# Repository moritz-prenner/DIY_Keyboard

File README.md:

# DIY_Keyboard 

This project is a full size Keyboard powered by a rp2040 pro micro and a custom pcb designed by myself :)
After I am going to build it it should (hopefully) function like a regular storebought keyboard. It even contains a knob to control volume for example.
I built this project to get better at pcb design and learn something new about keyboard firmware.

Note for the reviewer:

As you probably already seen, my total (in the bom) is around 95$. But this number is without the filament cost for the printing of the case. 
Even tho I am probably going to spend my tickets I am going to earn with this project on filament, I still estimated the cost and added it to the bom total.
That makes my funding request (around 120 - 130 $) - of course I am going to return the rest if it is cheaper than expected.

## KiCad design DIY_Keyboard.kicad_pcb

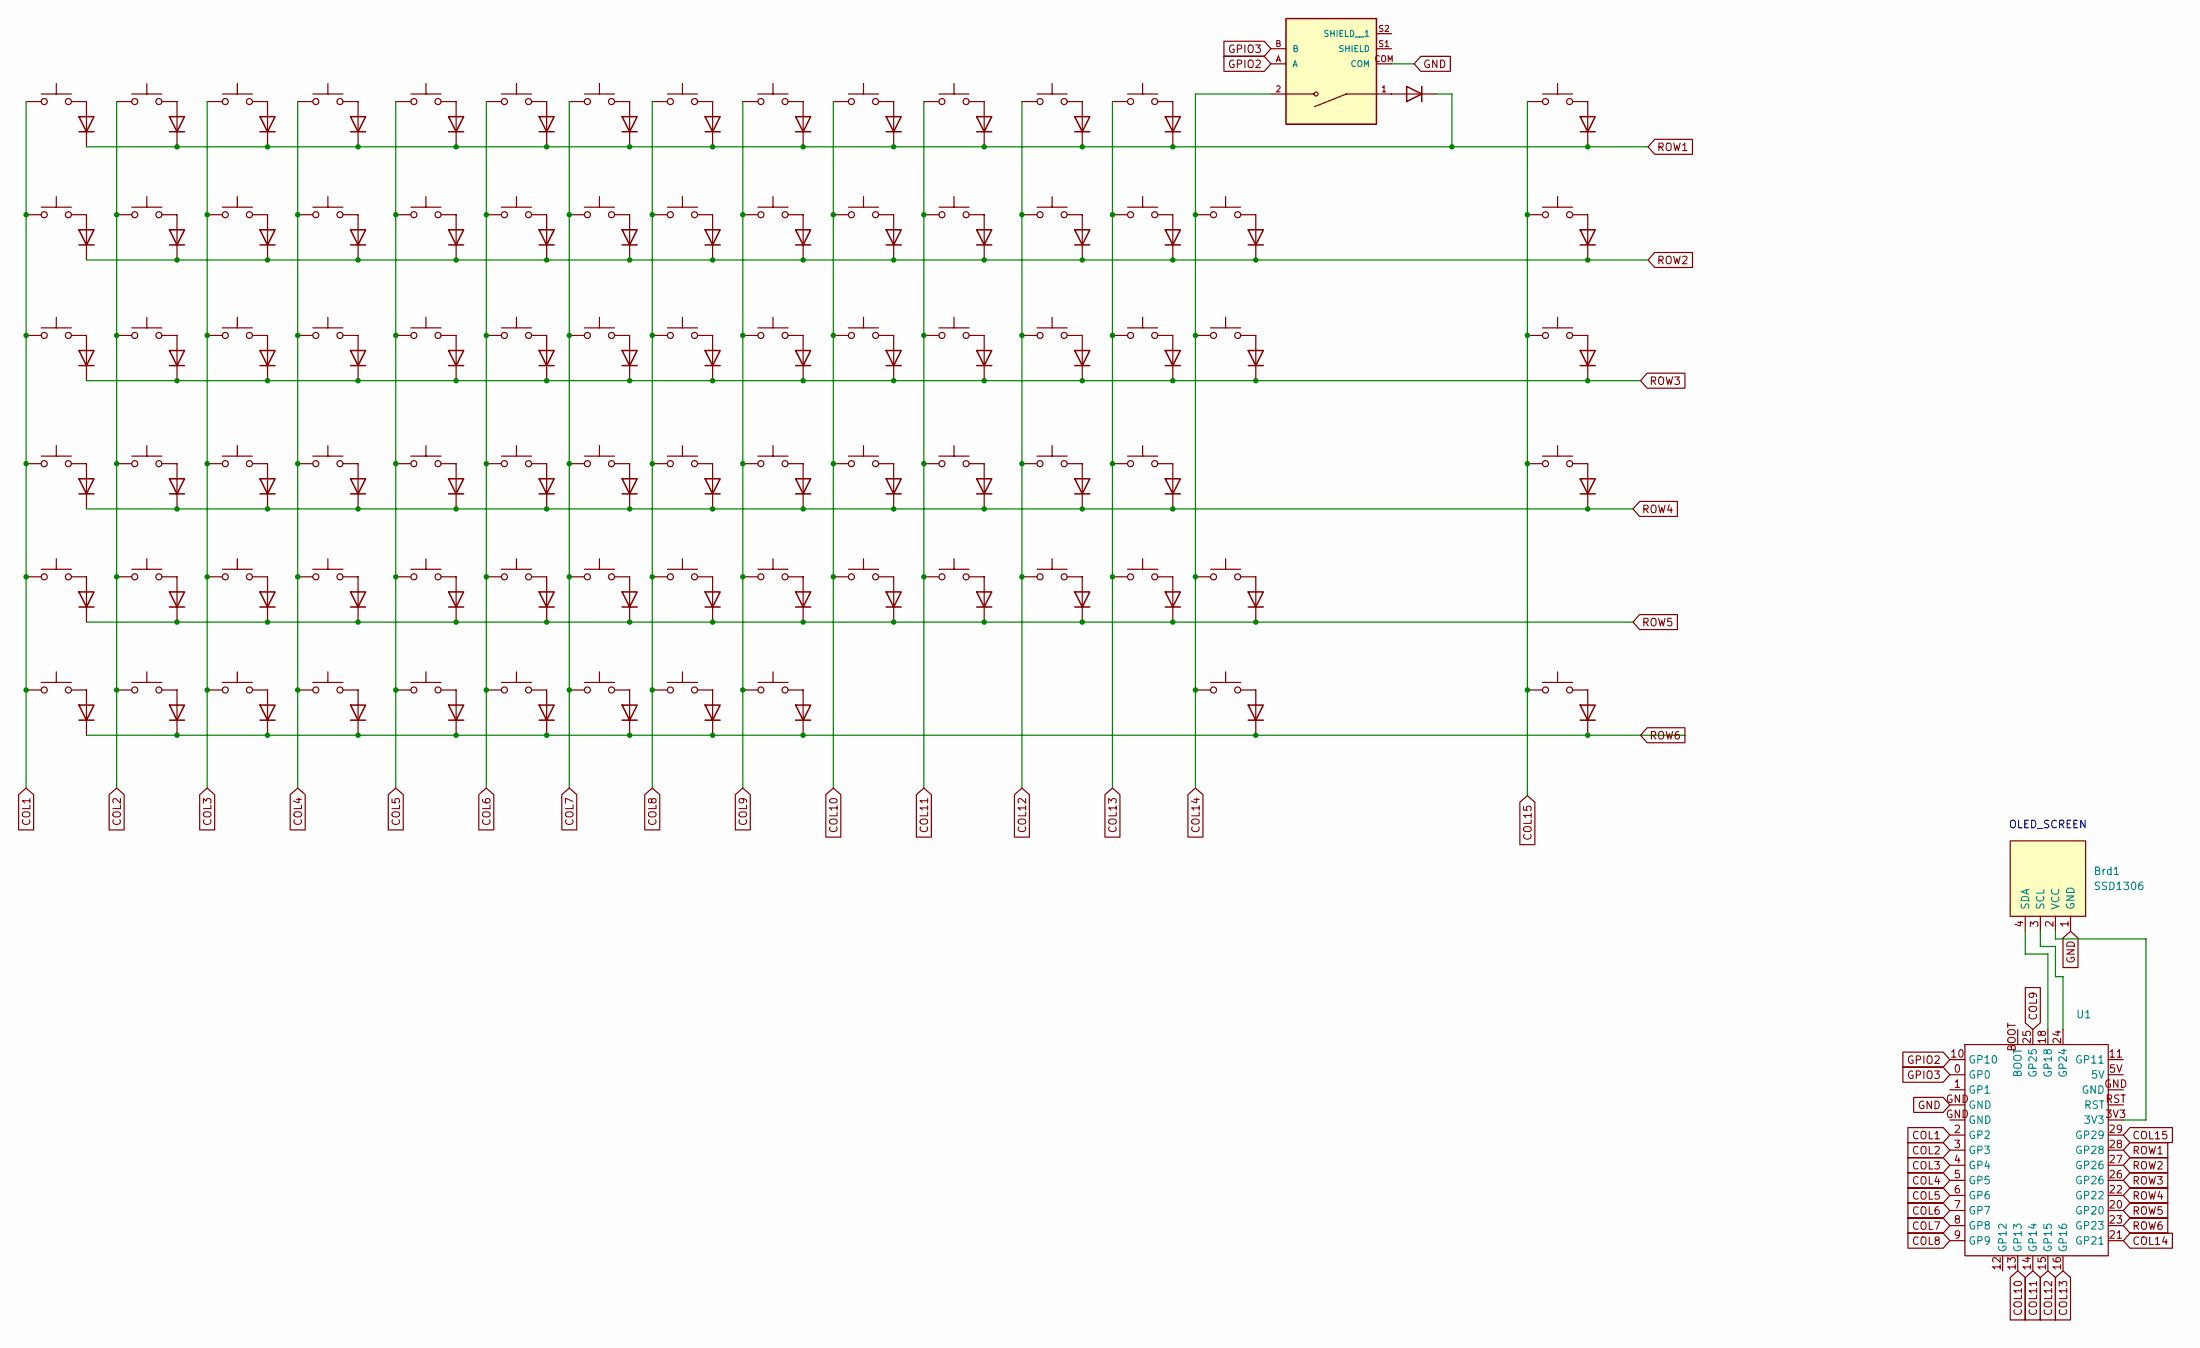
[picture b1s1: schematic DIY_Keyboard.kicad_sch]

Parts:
Brd1: SSD1306; oled_screen
D1, D2, D3, D4, D5, D6, D7, D8, D9, D10, D11, D12, D13, D14, D15, D16, D17, D18, D19, D20, D21, D22, D23, D24, D25, D26, D27, D28, D29, D30, D31, D32, D33, D34, D35, D36, D37, D38, D39, D40, D41, D42, D43, D44, D45, D46, D47, D48, D49, D50, D51, D52, D53, D54, D55, D56, D57, D58, D59, D60, D61, D62, D63, D64, D65, D66, D67, D68, D69, D70, D71, D72, D73, D74, D75, D76, D77, D78, D79, D80, D81, D82, D83, D85: 1N4148; Crystal_SMD_G8-2Pin_3.2x1.5mm_HandSoldering
MT1: PEC11R-4215F-S0024; XDCR_PEC11R-4215F-S0024; PARTREV Rev. 09/19
SW1, SW2, SW3, SW4, SW5, SW6, SW7, SW8, SW9, SW10, SW11, SW12, SW13, SW14, SW15, SW16, SW17, SW18, SW19, SW20, SW21, SW22, SW23, SW24, SW25, SW26, SW27, SW28, SW30, SW32, SW33, SW34, SW35, SW36, SW37, SW38, SW39, SW40, SW41, SW42, SW43, SW45, SW47, SW48, SW49, SW50, SW51, SW52, SW53, SW54, SW55, SW56, SW57, SW58, SW60, SW61, SW62, SW63, SW64, SW65, SW66, SW67, SW68, SW69, SW70, SW72, SW81, SW82, SW83: SW_Push; SW_Cherry_MX_1.00u_PCB
SW29: SW_Push; SW_Cherry_MX_2.00u_PCB
SW31: SW_Push; SW_Cherry_MX_1.50u_PCB
SW44: SW_Push; SW_Cherry_MX_ISOEnter_PCB_v2
SW46: SW_Push; SW_Cherry_MX_1.75u_PCB
SW59, SW73, SW74, SW75, SW77, SW78, SW79, SW80: SW_Push; SW_Cherry_MX_1.25u_PCB
SW71: SW_Push; SW_Cherry_MX_2.75u_PCB
SW76: SW_Push; SW_Cherry_MX_6.25u_PCB
U1: pro_micro_rp2040

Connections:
COL1: SW1.1, SW16.1, SW31.1, SW46.1, SW59.1, SW73.1, U1.2 (GP2)
COL2: SW2.1, SW17.1, SW32.1, SW47.1, SW60.1, SW74.1, U1.3 (GP3)
COL3: SW3.1, SW18.1, SW33.1, SW48.1, SW61.1, SW75.1, U1.4 (GP4)
COL4: SW4.1, SW19.1, SW34.1, SW49.1, SW62.1, SW76.1, U1.5 (GP5)
COL5: SW5.1, SW20.1, SW35.1, SW50.1, SW63.1, SW77.1, U1.6 (GP6)
COL6: SW6.1, SW21.1, SW36.1, SW51.1, SW64.1, SW78.1, U1.7 (GP7)
COL7: SW7.1, SW22.1, SW37.1, SW52.1, SW65.1, SW79.1, U1.8 (GP8)
COL8: SW8.1, SW23.1, SW38.1, SW53.1, SW66.1, SW80.1, U1.9 (GP9)
COL9: SW9.1, SW24.1, SW39.1, SW54.1, SW67.1, SW81.1, U1.25 (GP25)
COL10: SW10.1, SW25.1, SW40.1, SW55.1, SW68.1, U1.13 (GP13)
COL11: SW11.1, SW26.1, SW41.1, SW56.1, SW69.1, U1.14 (GP14)
COL12: SW12.1, SW27.1, SW42.1, SW57.1, SW70.1, U1.15 (GP15)
COL13: SW13.1, SW28.1, SW43.1, SW58.1, SW71.1, U1.16 (GP16)
COL14: MT1.2, SW29.1, SW44.1, SW72.1, SW82.1, U1.21 (GP21)
COL15: SW14.1, SW15.1, SW30.1, SW45.1, SW83.1, U1.29 (GP29)
GND: Brd1.1 (GND), MT1.COM, U1.GND
GPIO2: MT1.A, U1.10 (GP10)
GPIO3: MT1.B, U1.0 (GP0)
unnamed: Brd1.3 (SCL), U1.24 (GP24)
unnamed: Brd1.4 (SDA), U1.18 (GP18)
unnamed: Brd1.2 (VCC), U1.3V3
unnamed: D1.2 (A), SW1.2
unnamed: D2.2 (A), SW2.2
unnamed: D3.2 (A), SW3.2
unnamed: D4.2 (A), SW4.2
unnamed: D5.2 (A), SW5.2
unnamed: D6.2 (A), SW6.2
unnamed: D7.2 (A), SW7.2
unnamed: D8.2 (A), SW8.2
unnamed: D9.2 (A), SW9.2
unnamed: D10.2 (A), SW10.2
unnamed: D11.2 (A), SW11.2
unnamed: D12.2 (A), SW12.2
unnamed: D13.2 (A), SW13.2
unnamed: D14.2 (A), SW14.2
unnamed: D15.2 (A), SW15.2
unnamed: D16.2 (A), SW16.2
unnamed: D17.2 (A), SW17.2
unnamed: D18.2 (A), SW18.2
unnamed: D19.2 (A), SW19.2
unnamed: D20.2 (A), SW20.2
unnamed: D21.2 (A), SW21.2
unnamed: D22.2 (A), SW22.2
unnamed: D23.2 (A), SW23.2
unnamed: D24.2 (A), SW24.2
unnamed: D25.2 (A), SW25.2
unnamed: D26.2 (A), SW26.2
unnamed: D27.2 (A), SW27.2
unnamed: D28.2 (A), SW28.2
unnamed: D29.2 (A), SW29.2
unnamed: D30.2 (A), SW30.2
unnamed: D31.2 (A), SW31.2
unnamed: D32.2 (A), SW32.2
unnamed: D33.2 (A), SW33.2
unnamed: D34.2 (A), SW34.2
unnamed: D35.2 (A), SW35.2
unnamed: D36.2 (A), SW36.2
unnamed: D37.2 (A), SW37.2
unnamed: D38.2 (A), SW38.2
unnamed: D39.2 (A), SW39.2
unnamed: D40.2 (A), SW40.2
unnamed: D41.2 (A), SW41.2
unnamed: D42.2 (A), SW42.2
unnamed: D43.2 (A), SW43.2
unnamed: D44.2 (A), SW44.2
unnamed: D45.2 (A), SW45.2
unnamed: D46.2 (A), SW46.2
unnamed: D47.2 (A), SW47.2
unnamed: D48.2 (A), SW48.2
unnamed: D49.2 (A), SW49.2
unnamed: D50.2 (A), SW50.2
unnamed: D51.2 (A), SW51.2
unnamed: D52.2 (A), SW52.2
unnamed: D53.2 (A), SW53.2
unnamed: D54.2 (A), SW54.2
unnamed: D55.2 (A), SW55.2
unnamed: D56.2 (A), SW56.2
unnamed: D57.2 (A), SW57.2
unnamed: D58.2 (A), SW58.2
unnamed: D59.2 (A), SW59.2
unnamed: D60.2 (A), SW60.2
unnamed: D61.2 (A), SW61.2
unnamed: D62.2 (A), SW62.2
unnamed: D63.2 (A), SW63.2
unnamed: D64.2 (A), SW64.2
unnamed: D65.2 (A), SW65.2
unnamed: D66.2 (A), SW66.2
unnamed: D67.2 (A), SW67.2
unnamed: D68.2 (A), SW68.2
unnamed: D69.2 (A), SW69.2
unnamed: D70.2 (A), SW70.2
unnamed: D71.2 (A), SW71.2
unnamed: D72.2 (A), SW72.2
unnamed: D73.2 (A), SW73.2
unnamed: D74.2 (A), SW74.2
unnamed: D75.2 (A), SW75.2
unnamed: D76.2 (A), SW76.2
unnamed: D77.2 (A), SW77.2
unnamed: D78.2 (A), SW78.2
unnamed: D79.2 (A), SW79.2
unnamed: D80.2 (A), SW80.2
unnamed: D81.2 (A), SW81.2
unnamed: D82.2 (A), SW82.2
unnamed: D83.2 (A), SW83.2
unnamed: D85.2 (A), MT1.1
ROW1: D1.1 (K), D2.1 (K), D3.1 (K), D4.1 (K), D5.1 (K), D6.1 (K), D7.1 (K), D8.1 (K), D9.1 (K), D10.1 (K), D11.1 (K), D12.1 (K), D13.1 (K), D14.1 (K), D85.1 (K), U1.28 (GP28)
ROW2: D15.1 (K), D16.1 (K), D17.1 (K), D18.1 (K), D19.1 (K), D20.1 (K), D21.1 (K), D22.1 (K), D23.1 (K), D24.1 (K), D25.1 (K), D26.1 (K), D27.1 (K), D28.1 (K), D29.1 (K), U1.27 (GP26)
ROW3: D30.1 (K), D31.1 (K), D32.1 (K), D33.1 (K), D34.1 (K), D35.1 (K), D36.1 (K), D37.1 (K), D38.1 (K), D39.1 (K), D40.1 (K), D41.1 (K), D42.1 (K), D43.1 (K), D44.1 (K), U1.26 (GP26)
ROW4: D45.1 (K), D46.1 (K), D47.1 (K), D48.1 (K), D49.1 (K), D50.1 (K), D51.1 (K), D52.1 (K), D53.1 (K), D54.1 (K), D55.1 (K), D56.1 (K), D57.1 (K), D58.1 (K), U1.22 (GP22)
ROW5: D59.1 (K), D60.1 (K), D61.1 (K), D62.1 (K), D63.1 (K), D64.1 (K), D65.1 (K), D66.1 (K), D67.1 (K), D68.1 (K), D69.1 (K), D70.1 (K), D71.1 (K), D72.1 (K), U1.20 (GP20)
ROW6: D73.1 (K), D74.1 (K), D75.1 (K), D76.1 (K), D77.1 (K), D78.1 (K), D79.1 (K), D80.1 (K), D81.1 (K), D82.1 (K), D83.1 (K), U1.23 (GP23)

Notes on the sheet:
OLED_SCREEN

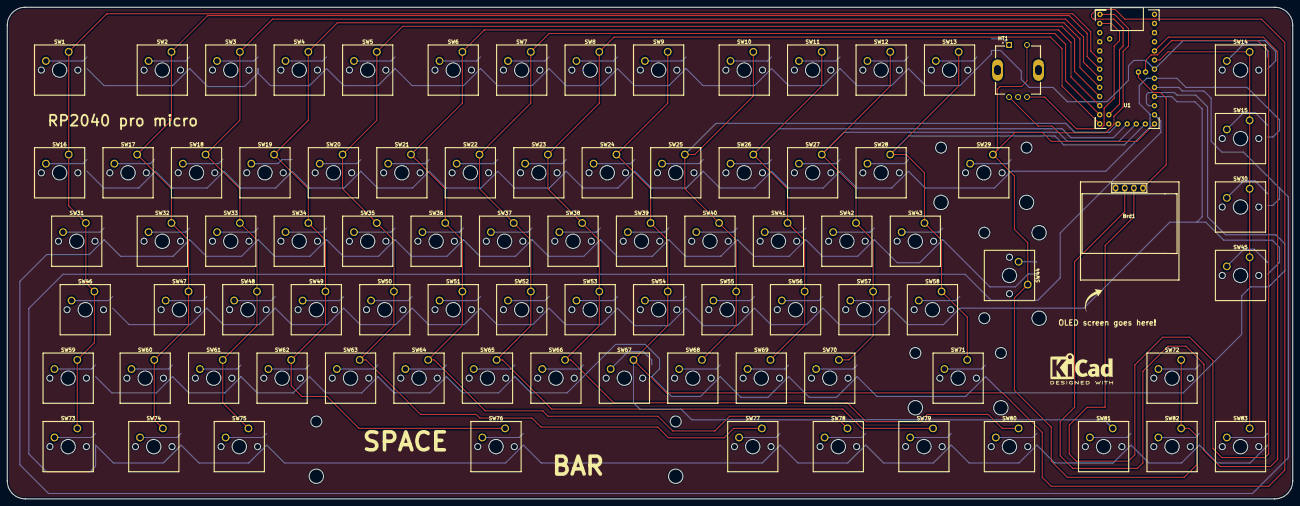
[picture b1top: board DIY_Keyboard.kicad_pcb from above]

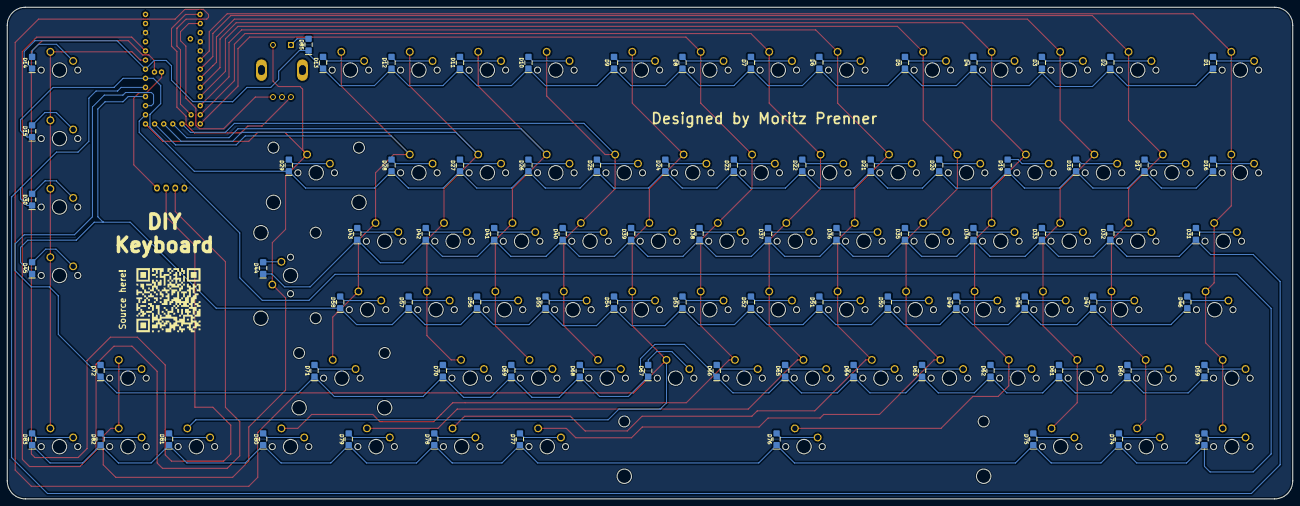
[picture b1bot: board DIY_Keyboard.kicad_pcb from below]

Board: 2 copper layers, 357.7 x 136.8 mm, 170 parts (84 on the bottom side), 111 nets.

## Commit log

2025-10-04 Create BOM
2025-10-04 Update BOM
2025-12-14 Add image upload placeholder to README
    Added an image upload placeholder to the README.
2025-12-14 Update README with new image and description
2025-12-16 Add test_cad file with initial content
2025-12-16 Add test_pcb file with initial content
2025-12-17 commit 2
2026-01-02 Create test_removed_later
